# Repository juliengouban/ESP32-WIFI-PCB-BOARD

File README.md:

# ESP32-WIFI-PCB-BOARD

The ESP32 is a microcontroller produced by Espressif Systems, a Chinese company specializing in wireless connectivity solutions. The ESP32 is the successor to the ESP8266, another popular microcontroller.

The ESP32 integrates advanced functionalities, including Wi-Fi and Bluetooth connectivity, making it suitable for a wide range of IoT applications. We've created a simple PCB based on the ESP32 Wifi microcontroller on Kidcad.

*Project duration: 3 days*

# Table of contents
- [Electronic diagram](#electronic-diagram)
- [PCB Design](#pcb-design)

## Electronic diagram

We'll now take a closer look at how our electronic board works:

To power our ESP32 Wi-Fi card, we've integrated a type B micro-USB connector, facilitating both program upload and card powering.

We've also added a +3.3V voltage regulator, as the ESP32 can't handle a 5V supply:

The ESP32 is supplied with +3.3V via the voltage regulator.

We've also integrated a 3-pin male connector for flash memory programming or program start-up:

An LED is connected to GPIO 1, allowing the GPIO pins on the ESP32 board to be tested by flashing the LED :

## PCB Design

The board is designed in two layers. On the top, we find the 3.3V voltage regulator and the Micro-USB type B connector. A ground plane has been added to the entire board, with the exception of the area around the Wi-Fi antenna at the bottom.

A ground plane (or a large metal surface) can interfere with the electromagnetic field generated by the antenna. The antenna is designed to transmit or receive radio waves (in the Wi-Fi frequency range, generally around 2.4 GHz or 5 GHz), and a ground plane under the antenna can interfere with the propagation of these waves by modifying the distribution of the electric or magnetic field around the antenna.

The design was carried out using KiCad, and manufacturing was entrusted to JLCPCB, at a cost of around fifteen euros.

Here is a 3d view of the PCB:

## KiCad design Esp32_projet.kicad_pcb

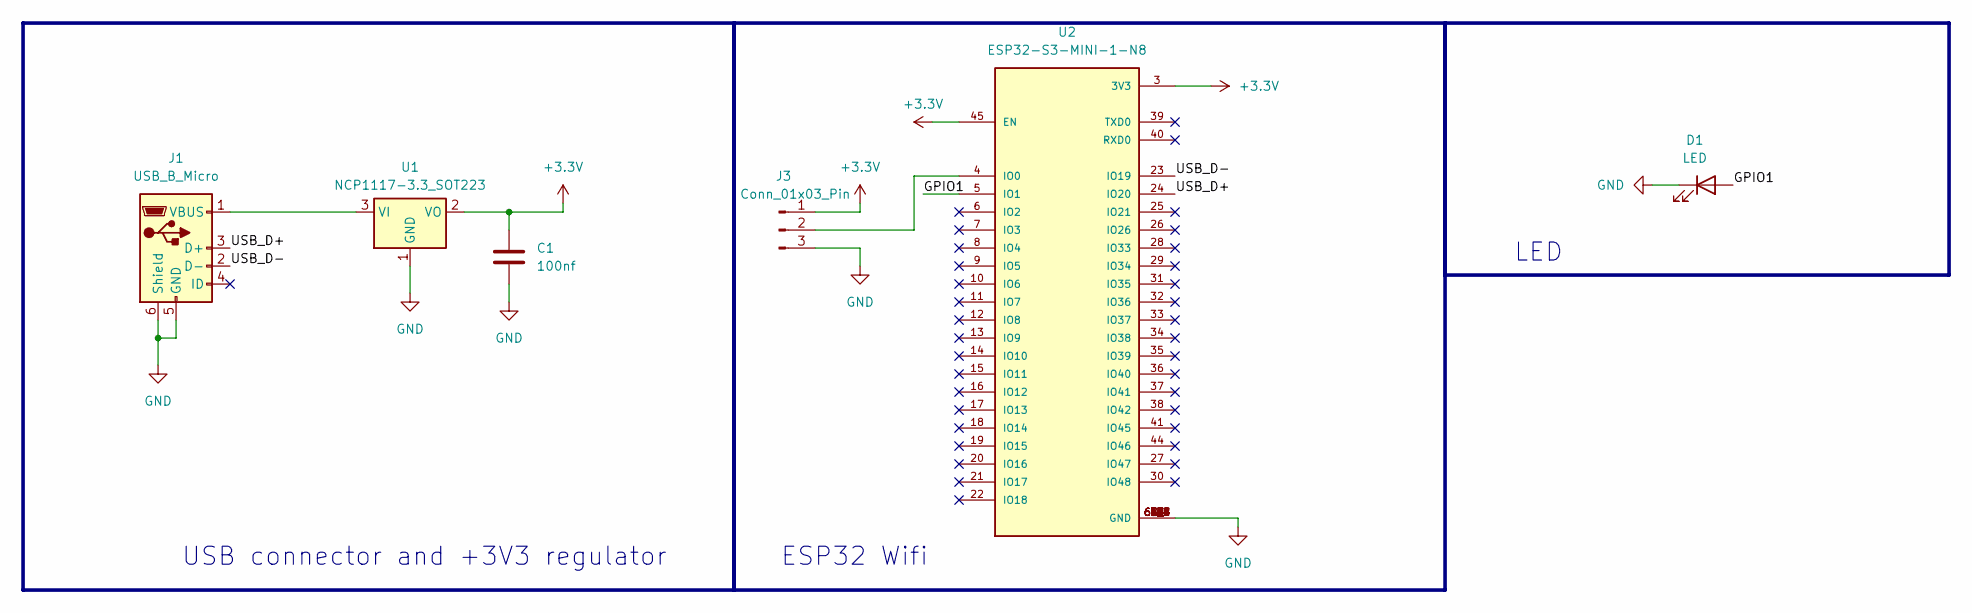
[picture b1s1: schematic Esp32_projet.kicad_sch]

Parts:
C1: 100nf; C_0402_1005Metric
D1: LED; LED_0402_1005Metric
J1: USB_B_Micro; USB_Micro-B_Amphenol_10103594-0001LF_Horizontal
J3: Conn_01x03_Pin; PinHeader_1x03_P1.27mm_Vertical
U1: NCP1117-3.3_SOT223; SOT-223-3_TabPin2
U2: ESP32-S3-MINI-1-N8; XCVR_ESP32-S3-MINI-1-N8; PARTREV v0.6

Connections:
+3.3V: C1.1, J3.1, U1.2 (VO), U2.3 (3V3), U2.45 (EN)
/GPIO1: D1.2 (A), U2.5 (IO1)
/USB_D+: J1.3 (D+), U2.24 (IO20)
/USB_D-: J1.2 (D-), U2.23 (IO19)
GND: C1.2, D1.1 (K), J1.5 (GND), J1.6 (Shield), J3.3, U1.1 (GND), U2.1 (GND), U2.2 (GND), U2.42 (GND), U2.43 (GND), U2.46 (GND), U2.47 (GND), U2.48 (GND), U2.49 (GND), U2.50 (GND), U2.51 (GND), U2.52 (GND), U2.53 (GND), U2.54 (GND), U2.55 (GND), U2.56 (GND), U2.57 (GND), U2.58 (GND), U2.59 (GND), U2.60 (GND), U2.61 (GND), U2.61_1 (GND), U2.61_2 (GND), U2.61_3 (GND), U2.61_4 (GND), U2.61_5 (GND), U2.61_6 (GND), U2.61_7 (GND), U2.61_8 (GND), U2.62 (GND), U2.63 (GND), U2.64 (GND), U2.65 (GND)
unnamed: J1.1 (VBUS), U1.3 (VI)
unnamed: J3.2, U2.4 (IO0)

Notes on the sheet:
LED
USB connector and +3V3 regulator
ESP32 Wifi

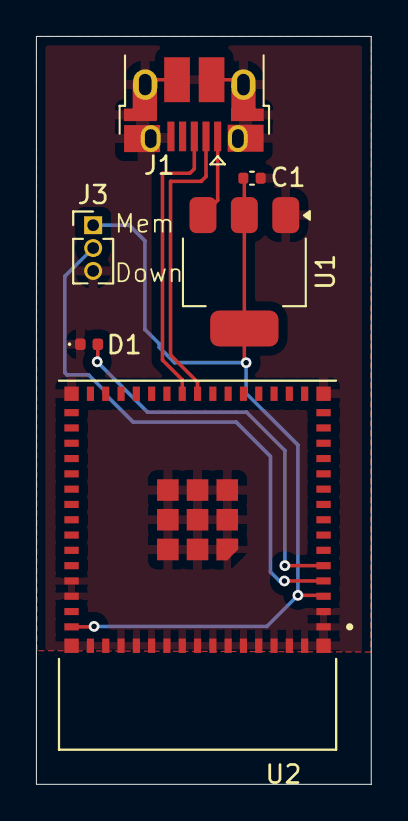
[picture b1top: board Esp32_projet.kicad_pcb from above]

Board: 2 copper layers, 18.6 x 41.5 mm, 6 parts (0 on the bottom side), 7 nets.

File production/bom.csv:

Designator,Footprint,Quantity,Value,LCSC Part #
C1,0402,1,100nf,
D1,0402,1,LED,
J1,USB_Micro-B_Amphenol_10103594-0001LF_Horizontal,1,USB_B_Micro,
J3,PinHeader_1x03_P1.27mm_Vertical,1,Conn_01x03_Pin,
U1,SOT-223-3_TabPin2,1,NCP1117-3.3_SOT223,
U2,XCVR_ESP32-S3-MINI-1-N8,1,ESP32-S3-MINI-1-N8,
